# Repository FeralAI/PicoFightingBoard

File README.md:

# Pico Fighting Board

Open source PCB for arcade sticks using Raspberry Pi Pico.

## Note

A newer community version of the firmware for the Raspberry Pi Pico can be found here : 
<a href=https://github.com/OpenStickCommunity/GP2040-CE>https://github.com/OpenStickCommunity/GP2040-CE</a>

## Introduction

They say imitation is the highest form of flattery. If that's the case then the Brook line of arcade controller boards must be blushing beet red. The Pico Fighting Board uses the same form factor and layout of the Brook PCBs to maintain compatibility with existing arcade stick cases, wiring harnesses, wire management accessories, etc.

The files for PCB production are in the [Releases](https://github.com/FeralAI/PicoFightingBoard/releases) section. The zip file contains the Gerber and drill files, which is all you'll need if you're soldering SMT components yourself. There are also `csv` files for the BOM (Bill of Materials) and component positioning for SMT assembly service.

## Components needed for assembling your own boards (soldering required)

Pico Fighting Board Components List v1.1a

Qty - Part
<br>1 - Raspberry Pi Pico (non wifi version)
<br>1 - SN74LV1T34DBVR Buffer / Logic chip 5-Pin SOT-2
<br>10 - Screw Terminal Block 2 pins / 3.5mm pitch (other combinations should work)
<br>4 - 4 pin JST-PH 2.0 mm pitch Vertical through hole conn
<br>1 - 5 pin JST-PH 2.0 mm pitch Vertical through hole conn
<br>1 - 2 x 10 2.54 mm pitch Pin header vertical type (2 individual 10 pin ones will work)
<br>1 - 2 x 1 2.54 mm pitch Pin header vertical type
<br>2 - 4 pin JST-SH 1.0 mm pitch Vertical surface mount conn
<br>5 - 330 ohm Resistor 0805 SMD type
<br>2 - 4.7k ohm Capacitor 0805 SMD type
<br>1 - 0.1 uF (100nF) Capacitor 0805 SMD type

## Component Location

## Firmware

The [GP2040](https://github.com/FeralAI/GP2040) gamepad firmware for Pi Pico/RP2040 has a pre-configured build for use with the Pico Fighting Board, providing support for XInput (PC, Android, Raspberry Pi, etc.), DInput (PC/PS3) and Nintendo Switch. [Go to the releases](https://github.com/FeralAI/GP2040/releases) and download the `GP2040-PicoFightingBoard.uf2`. To flash:

1. Unplug your Pico Fighting Board.
1. Hold the BOOTSEL button on the Pico and plug into your computer. A new removable drive named `RPI-RP2` should appear in your file explorer.
1. Drag and drop the `GP2040-PicoFightingBoard.uf2` file into the removable drive. This will flash the board.
1. The board should now be running the GP2040 firmware and should appear as a controller on your computer.

## Modification

If you want to modify the PCB layout you'll need the free [KiCad software](https://www.kicad.org/download/) installed. KiCad 5.1.9 was used for these instructions.

### Libraries

The [`libraries`](https://github.com/FeralAI/PicoFightingBoard/tree/main/libraries) folder contains the schematics and footprints required to work with the KiCad source files.

#### Symbols

1. From the KiCad `Preferences` menu, select `Manage Symbol Libraries...`.
1. In the `Global Libraries` tab, click the folder icon.
1. Navigate to this repository, then navigate to `libraries/RP-Pico Libraries` and select the `MCU_RaspberryPi_and_Boards.lib` file.
1. Click `OK` to finish.

#### Footprints

1. From the KiCad `Preferences` menu, select `Manage Footprint Libraries...`.
1. In the `Global Libraries` tab, click the folder icon.
1. In the `Select Libary` dialog, navigate to `libraries/RP-Pico Libraries/MCU_RaspberryPi_and_Boards.pretty` in this repository.
1. Click `OK` to confirm the folder selection.
1. Repeat the same process for the `libraries/FeralAI/FeralAI.pretty` folder.
1. Click `OK` to finish.

## Support

If you would like to discuss and issues or features with the Pico Fighting Board, please join the [OpenStick Pico Fighting Board Discord channel](https://discord.gg/ZGfT68AvpG).

## Contributions

Want to help improve the Pico Fighting Board? There are a bunch of ways to contribute!

### Pull Requests

Pull requests are welcome and encouraged for enhancements, fixes and documentation updates.

### Donations

If you'd like to make a donation to my open source work, you can

or

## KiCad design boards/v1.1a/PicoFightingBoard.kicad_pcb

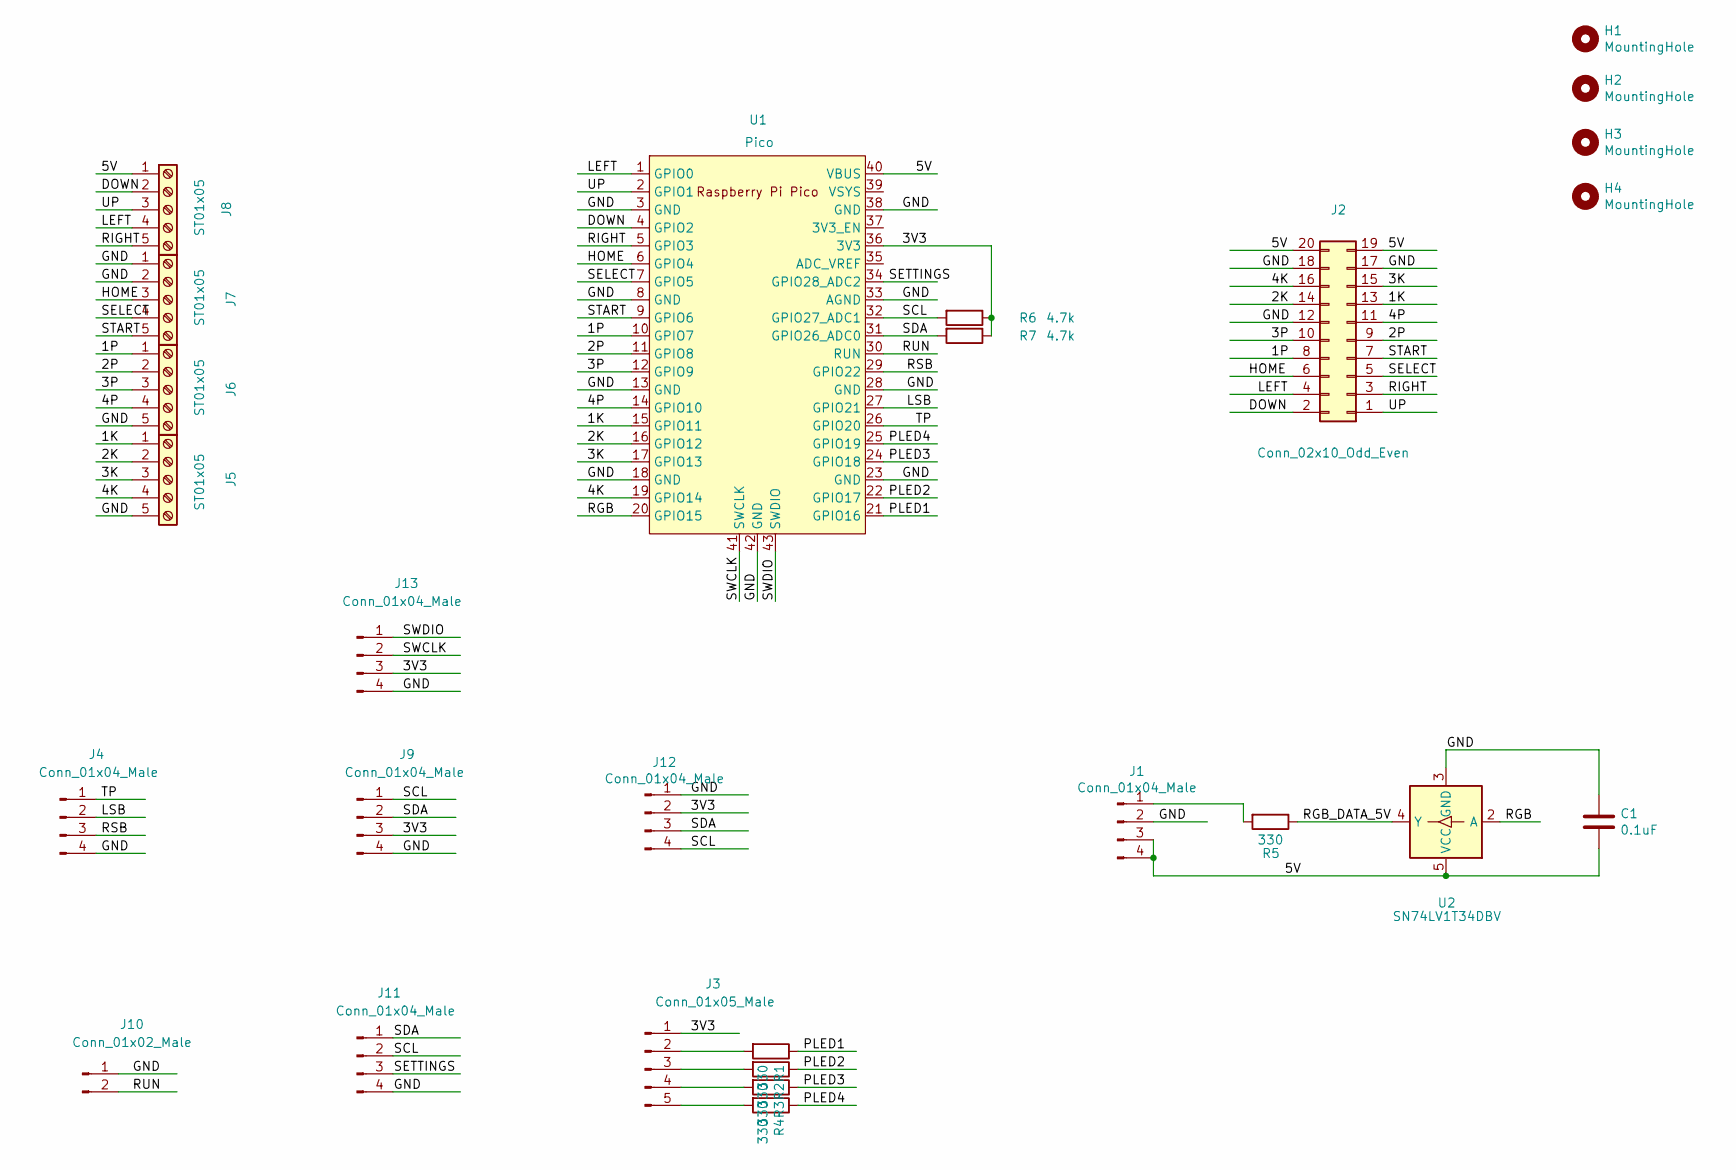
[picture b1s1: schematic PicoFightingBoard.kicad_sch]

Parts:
C1: 0.1uF; C_0805_2012Metric
H1, H2, H3, H4: MountingHole; MountingHole_3.5mm
J1, J4, J11, J12: Conn_01x04_Male; JST_PH_B4B-PH-K_1x04_P2.00mm_Vertical
J2: Conn_02x10_Odd_Even; PinHeader_2x10_P2.54mm_Vertical
J3: Conn_01x05_Male; JST_PH_B5B-PH-K_1x05_P2.00mm_Vertical
J5, J6, J7, J8: ST01x05; TerminalBlock_MetzConnect_Type059_RT06305HBWC_1x05_P3.50mm_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
J9, J13: Conn_01x04_Male; BOOM_SH_C145961_1x04_P1.00mm_Vertical
J10: Conn_01x02_Male; PinHeader_1x02_P2.54mm_Vertical
R1, R2, R3, R4, R5: 330; R_0805_2012Metric
R6, R7: 4.7k; R_0805_2012Metric
U1: Pico; RPi_Pico_SMD_TH_Clean
U2: SN74LV1T34DBV; SOT-23-5

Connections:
/1K: J2.13, J5.1, U1.15 (GPIO11)
/1P: J2.8, J6.1, U1.10 (GPIO7)
/2K: J2.14, J5.2, U1.16 (GPIO12)
/2P: J2.9, J6.2, U1.11 (GPIO8)
/3K: J2.15, J5.3, U1.17 (GPIO13)
/3P: J2.10, J6.3, U1.12 (GPIO9)
/3V3: J3.1, J9.3, J12.2, J13.3, R6.1, R7.1, U1.36 (3V3)
/4K: J2.16, J5.4, U1.19 (GPIO14)
/4P: J2.11, J6.4, U1.14 (GPIO10)
/5V: C1.2, J1.3, J1.4, J2.19, J2.20, J8.1, U1.40 (VBUS), U2.5 (VCC)
/DOWN: J2.2, J8.2, U1.4 (GPIO2)
/GND: C1.1, J1.2, J2.12, J2.17, J2.18, J4.4, J5.5, J6.5, J7.1, J7.2, J9.4, J10.1, J11.4, J12.1, J13.4, U1.3 (GND), U1.8 (GND), U1.13 (GND), U1.18 (GND), U1.23 (GND), U1.28 (GND), U1.33 (AGND), U1.38 (GND), U1.42 (GND), U2.3 (GND)
/HOME: J2.6, J7.3, U1.6 (GPIO4)
/LEFT: J2.4, J8.4, U1.1 (GPIO0)
/LSB: J4.2, U1.27 (GPIO21)
/PLED1: R1.1, U1.21 (GPIO16)
/PLED2: R2.1, U1.22 (GPIO17)
/PLED3: R3.1, U1.24 (GPIO18)
/PLED4: R4.1, U1.25 (GPIO19)
/RGB: U1.20 (GPIO15), U2.2 (A)
/RGB_DATA_5V: R5.1, U2.4 (Y)
/RIGHT: J2.3, J8.5, U1.5 (GPIO3)
/RSB: J4.3, U1.29 (GPIO22)
/RUN: J10.2, U1.30 (RUN)
/SCL: J9.1, J11.2, J12.4, R6.2, U1.32 (GPIO27_ADC1)
/SDA: J9.2, J11.1, J12.3, R7.2, U1.31 (GPIO26_ADC0)
/SELECT: J2.5, J7.4, U1.7 (GPIO5)
/SETTINGS: J11.3, U1.34 (GPIO28_ADC2)
/START: J2.7, J7.5, U1.9 (GPIO6)
/SWCLK: J13.2, U1.41 (SWCLK)
/SWDIO: J13.1, U1.43 (SWDIO)
/TP: J4.1, U1.26 (GPIO20)
/UP: J2.1, J8.3, U1.2 (GPIO1)
unnamed: J1.1, R5.2
unnamed: J3.2, R1.2
unnamed: J3.3, R2.2
unnamed: J3.4, R3.2
unnamed: J3.5, R4.2

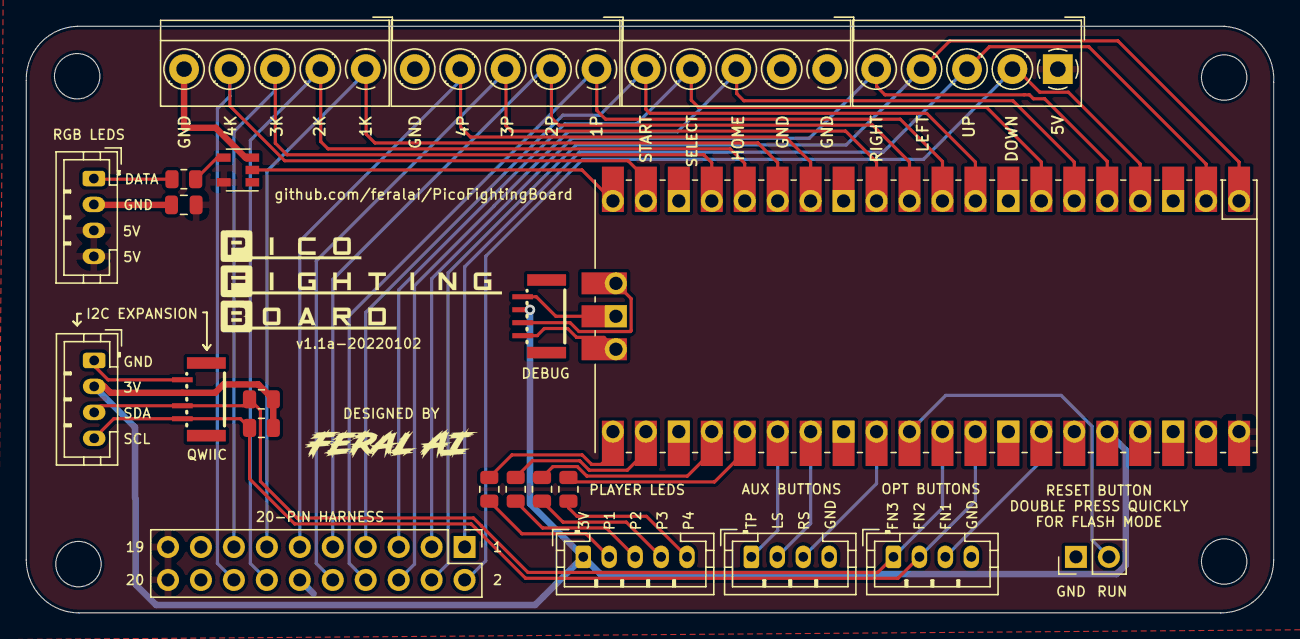
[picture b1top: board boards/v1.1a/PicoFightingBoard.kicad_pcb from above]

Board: 2 copper layers, 96.1 x 45.2 mm, 27 parts (0 on the bottom side), 38 nets.

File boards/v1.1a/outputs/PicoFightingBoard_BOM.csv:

Comment,Designator,Footprint,LCSC
0.1uF,C1,Capacitor_SMD:C_0805_2012Metric,C286511
Conn_01x02_Male,J10,Connector_JST:JST_XH_B2B-XH-A_1x02_P2.54mm_Vertical,C234182
Conn_02x10_Odd_Even,J2,Connector_PinHeader_2.54mm:PinHeader_2x10_P2.54mm_Vertical,C492427
Conn_01x05_Male,J3,Connector_JST:JST_PH_S5B-PH-K_1x05_P2.00mm_Vertical,C157993
Conn_01x04_Male,"J1,J4,J11,J12",Connector_JST:JST_PH_S4B-PH-K_1x04_P2.00mm_Vertical,C131334
Conn_01x04_Male,"J9,J13",Connector_JST:JST_SH_BM04B-SRSS-TB_1x04-1MP_P1.00mm_Vertical,C145961
330,"R1,R2,R3,R4,R5",Resistor_SMD:R_0805_2012Metric,C17630
4.7k,"R6,R7",Resistor_SMD:R_0805_2012Metric,C17673
SN74LV1T34DBV,U2,Package_TO_SOT_SMD:SOT-23-5,C100024

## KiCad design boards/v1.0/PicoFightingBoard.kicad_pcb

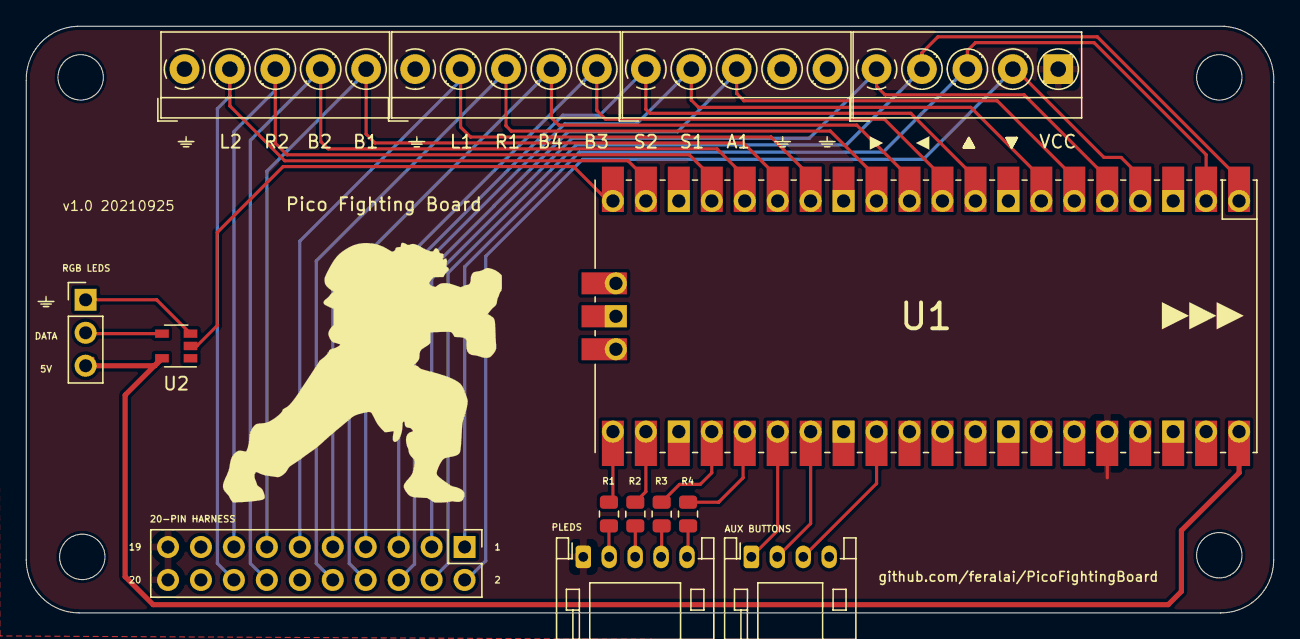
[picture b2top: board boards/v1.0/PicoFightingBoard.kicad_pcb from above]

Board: 2 copper layers, 96.1 x 45.2 mm, 20 parts (0 on the bottom side), 31 nets.

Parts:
20-PIN HARNESS: Conn_02x10_Odd_Even; PinHeader_2x10_P2.54mm_Vertical
 : GS_Ground_back
 #2,  #3,  #4,  #5,  #6: GS_Ground
AUX BUTTONS: Conn_01x04_Male; JST_PH_S4B-PH-K_1x04_P2.00mm_Horizontal
J5, J6, J7, J8: Screw_Terminal_01x05; TerminalBlock_MetzConnect_Type059_RT06305HBWC_1x05_P3.50mm_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
PLEDS: Conn_01x05_Male; JST_PH_S5B-PH-K_1x05_P2.00mm_Horizontal
R1, R2, R3, R4: 330; R_0805_2012Metric
RGB LEDS: Conn_01x03_Male; PinHeader_1x03_P2.54mm_Vertical
U1: Pico; RPi_Pico_SMD_TH_Clean
U2: SN74LV1T34DBV; SOT-23-5

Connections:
/3V: 20-PIN HARNESS.19, 20-PIN HARNESS.20, J8.5, PLEDS.1, U1.36
/GND: 20-PIN HARNESS.12, 20-PIN HARNESS.17, 20-PIN HARNESS.18, AUX BUTTONS.4, J5.1, J6.1, J7.4, J7.5, RGB LEDS.1, U1.38, U2.3
unnamed: 20-PIN HARNESS.1, J8.3, U1.2
unnamed: 20-PIN HARNESS.2, J8.4, U1.4
unnamed: 20-PIN HARNESS.3, J8.1, U1.5
unnamed: 20-PIN HARNESS.4, J8.2, U1.1
unnamed: 20-PIN HARNESS.5, J7.2, U1.7
unnamed: 20-PIN HARNESS.6, J7.3, U1.6
unnamed: 20-PIN HARNESS.7, J7.1, U1.9
unnamed: 20-PIN HARNESS.8, J6.5, U1.10
unnamed: 20-PIN HARNESS.9, J6.4, U1.11
unnamed: 20-PIN HARNESS.10, J6.3, U1.12
unnamed: 20-PIN HARNESS.11, J6.2, U1.14
unnamed: 20-PIN HARNESS.13, J5.5, U1.15
unnamed: 20-PIN HARNESS.14, J5.4, U1.16
unnamed: 20-PIN HARNESS.15, J5.3, U1.17
unnamed: 20-PIN HARNESS.16, J5.2, U1.19
unnamed: PLEDS.2, R1.2
unnamed: PLEDS.3, R2.2
unnamed: PLEDS.4, R3.2
unnamed: PLEDS.5, R4.2
unnamed: AUX BUTTONS.1, U1.26
unnamed: AUX BUTTONS.2, U1.27
unnamed: AUX BUTTONS.3, U1.29
unnamed: R1.1, U1.21
unnamed: R2.1, U1.22
unnamed: R3.1, U1.24
unnamed: R4.1, U1.25
unnamed: RGB LEDS.2, U2.4
unnamed: RGB LEDS.3, U1.40, U2.5
unnamed: U1.20, U2.2

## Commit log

2021-10-09 Fix typo
2021-10-14 Add GP2040 configs
2021-11-23 Add Discord link
2021-12-03 Fix pin 12 ground on 20-pin connector
2021-12-03 WIP for v1.1
2021-12-05 Commit latest rev
2021-12-05 Almost there
2021-12-05 Latest v1.1 rev
2021-12-06 Commit output files
2021-12-11 Update v1.1 to final
2021-12-28 Doc updates
2021-12-31 Add v1.1a rev
2022-01-02 Update to KiCad 6.0.0 for v1.1a board
2022-01-02 v1.1a final?!?
2022-01-11 Add contribution section to README
2022-01-11 Add url
2023-04-20 Remove store link
